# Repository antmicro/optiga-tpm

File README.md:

# Optiga TPM Module

Copyright (c) 2026 [Antmicro](https://www.antmicro.com)

## Overview

This project contains open hardware design files for a TPM 2.0 module based on the Infineon OPTIGA TPM SLB 9672. TPM module provides an SPI-connected TPM 2.0 IC for embedded systems, IoT, networking equipment, telecommunications infrastructure and consumer electronics.
It provides a foundation for securely establihing the identity and software status of connected devices.

The board connects to a host via SPI protocol and 3 GPIO pins. 
The Optiga TPM Module can be connected to various platforms with ERF5 40-pin board to board connector. All signals are exposed on testpads. 

The PCB design files were prepared in KiCad 10.x.

## Key features

* Trusted Platform Module (TPM) 2.0 compliant
* PQC-protected firmware update mechanism
* 40-pin ERF5 connector (compatible with Antmicro CM4 Baseboard)
* All signals exposed on testpads 
* 20 x 29 mm (0.78 x 1.14 inch) PCB outline

## Project structure

The main directory contains KiCad PCB project files, the LICENSE, and this README, and the img directory contains graphics for this README.

## License

This project is licensed under the [Apache-2.0](LICENSE) license.

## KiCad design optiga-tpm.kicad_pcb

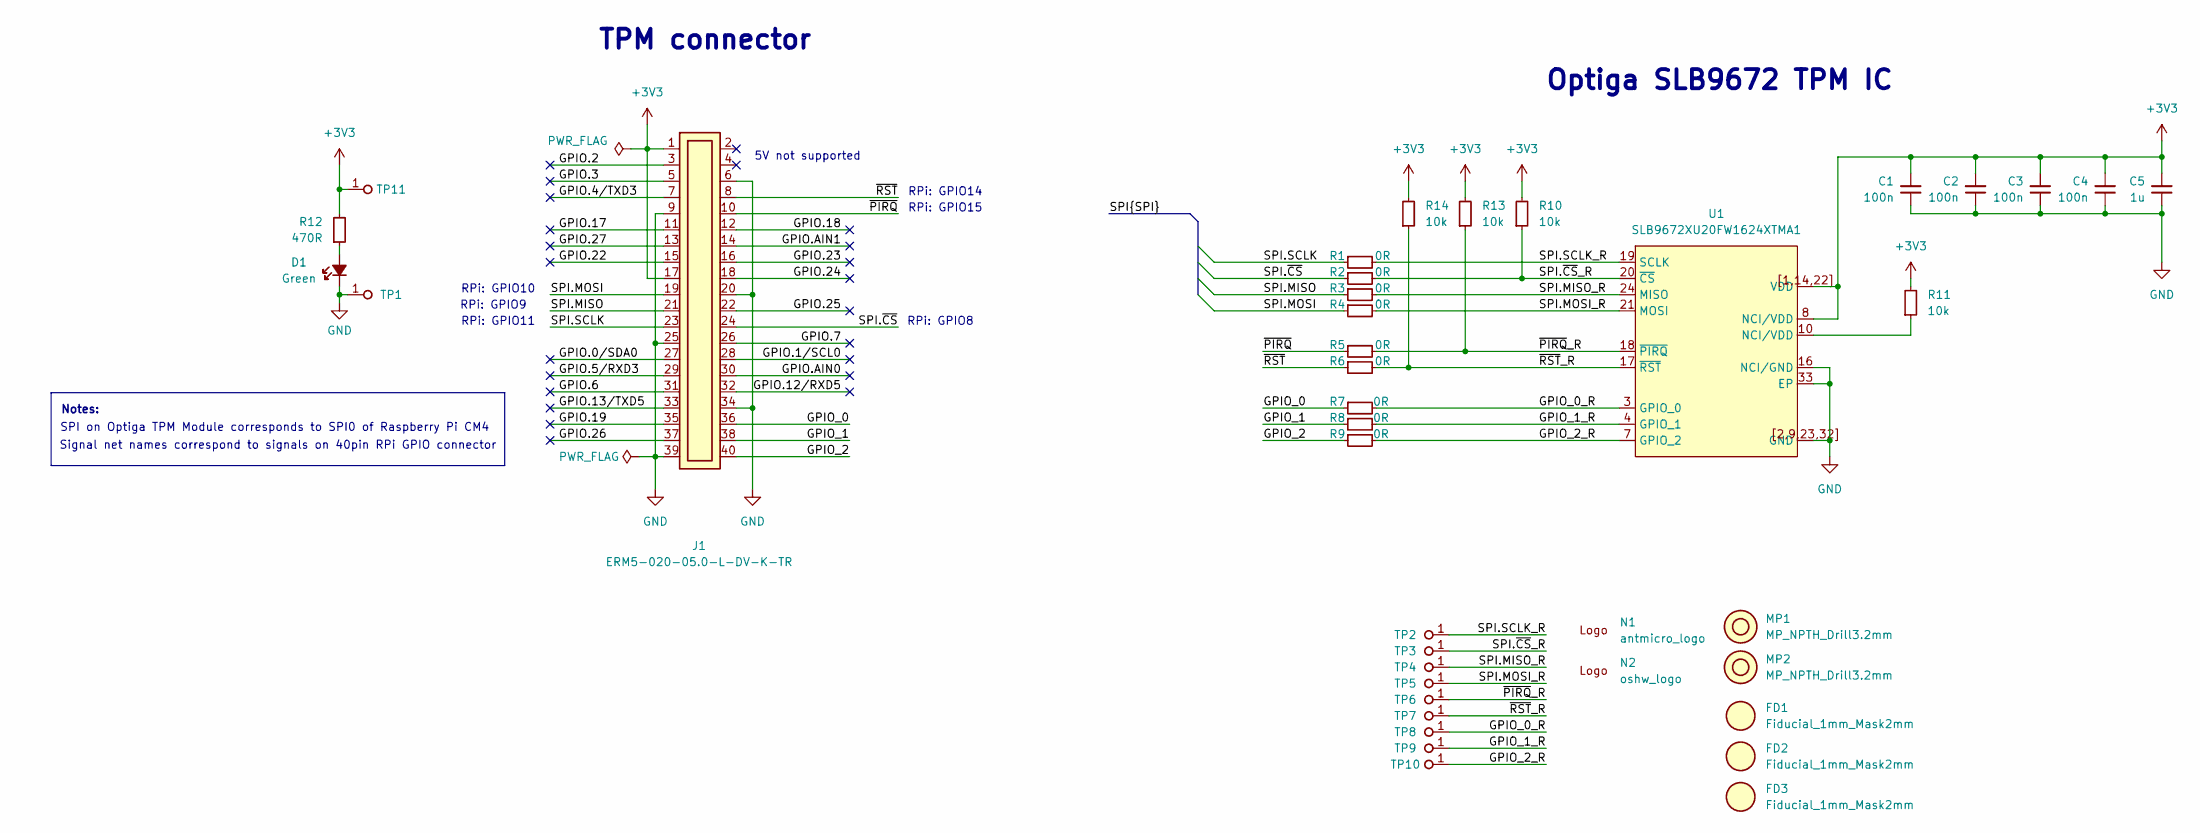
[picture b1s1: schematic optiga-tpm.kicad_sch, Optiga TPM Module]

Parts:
C1, C2, C3, C4: C_100n_25V_0402; C_0402_1005Metric; Voltage 25V; MPN CL05A104KA5NNNC
C5: C_1u_10V_X7R_0402; C_0402_1005Metric; Voltage 10V; MPN GRM155Z71A105KE01D
D1: LED_G_0603_KP-1608CGCK; LED_0603_1608Metric_G; MPN KP-1608CGCK
FD1, FD2, FD3: Fiducial_1mm_Mask2mm
J1: Plug_Samtec_ERM5_2x20_ERM5-020-05.0-L-DV-K-TR; Conn_Plug_Samtec_ERM5_2x20_ERM5-020-05.0-L-DV-K-TR; MPN ERM5-020-05.0-L-DV-K-TR
MP1, MP2: MP_NPTH_Drill3.2mm
N1: antmicro_logo; antmicro-logo_scaled_12mm
N2: oshw_logo; oshw-logo
R1, R2, R3, R4, R5, R6, R7, R8, R9: R_0R_0402; R_0402_1005Metric; MPN ERJ2GE0R00X
R10, R11, R13, R14: R_10k_0402; R_0402_1005Metric; Tolerance 1%; MPN CR0402-FX-1002GLF
R12: R_470R_0402; R_0402_1005Metric; Tolerance 1%; MPN CR0402-FX-4700GLF
TP1, TP2, TP3, TP4, TP5, TP6, TP7, TP8, TP9, TP10, TP11: TP_0.75mm_SMD; TP_SMD_0.75mm
U1: SLB9672XU20FW1624XTMA1; UQFN-32-1EP_5x5mm_P0.5mm_EP3.6x3.6mm; MPN SLB9672XU20FW1624XTMA1

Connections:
+3V3: C1.2, C2.2, C3.2, C4.2, C5.2, J1.1, J1.17, R10.2, R11.2, R12.2, R13.2, R14.2, TP11.1 (1_1), U1.1 (VDD), U1.8 (NCI/VDD), U1.14 (VDD), U1.22 (VDD), U1.[1,14,22] (VDD)
/GPIO.0/SDA0: J1.27
/GPIO.1/SCL0: J1.28
/GPIO.2: J1.3
/GPIO.3: J1.5
/GPIO.4/TXD3: J1.7
/GPIO.5/RXD3: J1.29
/GPIO.6: J1.31
/GPIO.7: J1.26
/GPIO.12/RXD5: J1.32
/GPIO.13/TXD5: J1.33
/GPIO.17: J1.11
/GPIO.18: J1.12
/GPIO.19: J1.35
/GPIO.22: J1.15
/GPIO.23: J1.16
/GPIO.24: J1.18
/GPIO.25: J1.22
/GPIO.26: J1.37
/GPIO.27: J1.13
/GPIO.AIN0: J1.30
/GPIO.AIN1: J1.14
/GPIO_0: J1.36, R7.1
/GPIO_0_R: R7.2, TP8.1 (1_1), U1.3 (GPIO_0)
/GPIO_1: J1.38, R8.1
/GPIO_1_R: R8.2, TP9.1 (1_1), U1.4 (GPIO_1)
/GPIO_2: J1.40, R9.1
/GPIO_2_R: R9.2, TP10.1 (1_1), U1.7 (GPIO_2)
/SPI.MISO: J1.21, R3.1
/SPI.MISO_R: R3.2, TP4.1 (1_1), U1.24 (MISO)
/SPI.MOSI: J1.19, R4.1
/SPI.MOSI_R: R4.2, TP5.1 (1_1), U1.21 (MOSI)
/SPI.SCLK: J1.23, R1.1
/SPI.SCLK_R: R1.2, TP2.1 (1_1), U1.19 (SCLK)
/SPI.~CS: J1.24, R2.1
/SPI.~CS_R: R2.2, R10.1, TP3.1 (1_1), U1.20 (~CS)
/~PIRQ: J1.10, R5.1
/~PIRQ_R: R5.2, R13.1, TP6.1 (1_1), U1.18 (~PIRQ)
/~RST: J1.8, R6.1
/~RST_R: R6.2, R14.1, TP7.1 (1_1), U1.17 (~RST)
GND: C1.1, C2.1, C3.1, C4.1, C5.1, D1.1 (C), J1.6, J1.9, J1.20, J1.25, J1.34, J1.39, TP1.1 (1_1), U1.2 (GND), U1.9 (GND), U1.16 (NCI/GND), U1.23 (GND), U1.32 (GND), U1.33 (EP), U1.[2,9,23,32] (GND)
unnamed: D1.2 (A), R12.1
unnamed: R11.1, U1.10 (NCI/VDD)

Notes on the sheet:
RPi: GPIO8
RPi: GPIO15
Optiga SLB9672 TPM IC
RPi: GPIO9
Signal net names correspond to signals on 40pin RPi GPIO connector
TPM connector
5V not supported
RPi: GPIO10
RPi: GPIO11
SPI on Optiga TPM Module corresponds to SPI0 of Raspberry Pi CM4
RPi: GPIO14
Notes:

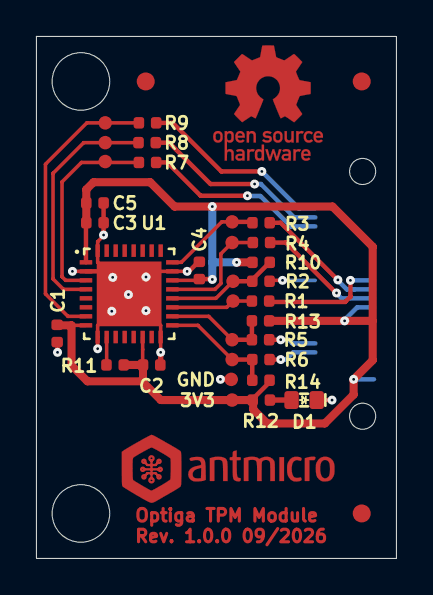
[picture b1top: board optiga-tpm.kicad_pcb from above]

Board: 2 copper layers, 20.0 x 29.0 mm, 40 parts (1 on the bottom side), 22 nets.

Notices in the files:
parts and their libraries:
Licence: Apache-2.0
License: Apache-2.0
